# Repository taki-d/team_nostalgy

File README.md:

# team_nostalgy
for meister

# library
## web
https://github.com/nkapliev/nixie

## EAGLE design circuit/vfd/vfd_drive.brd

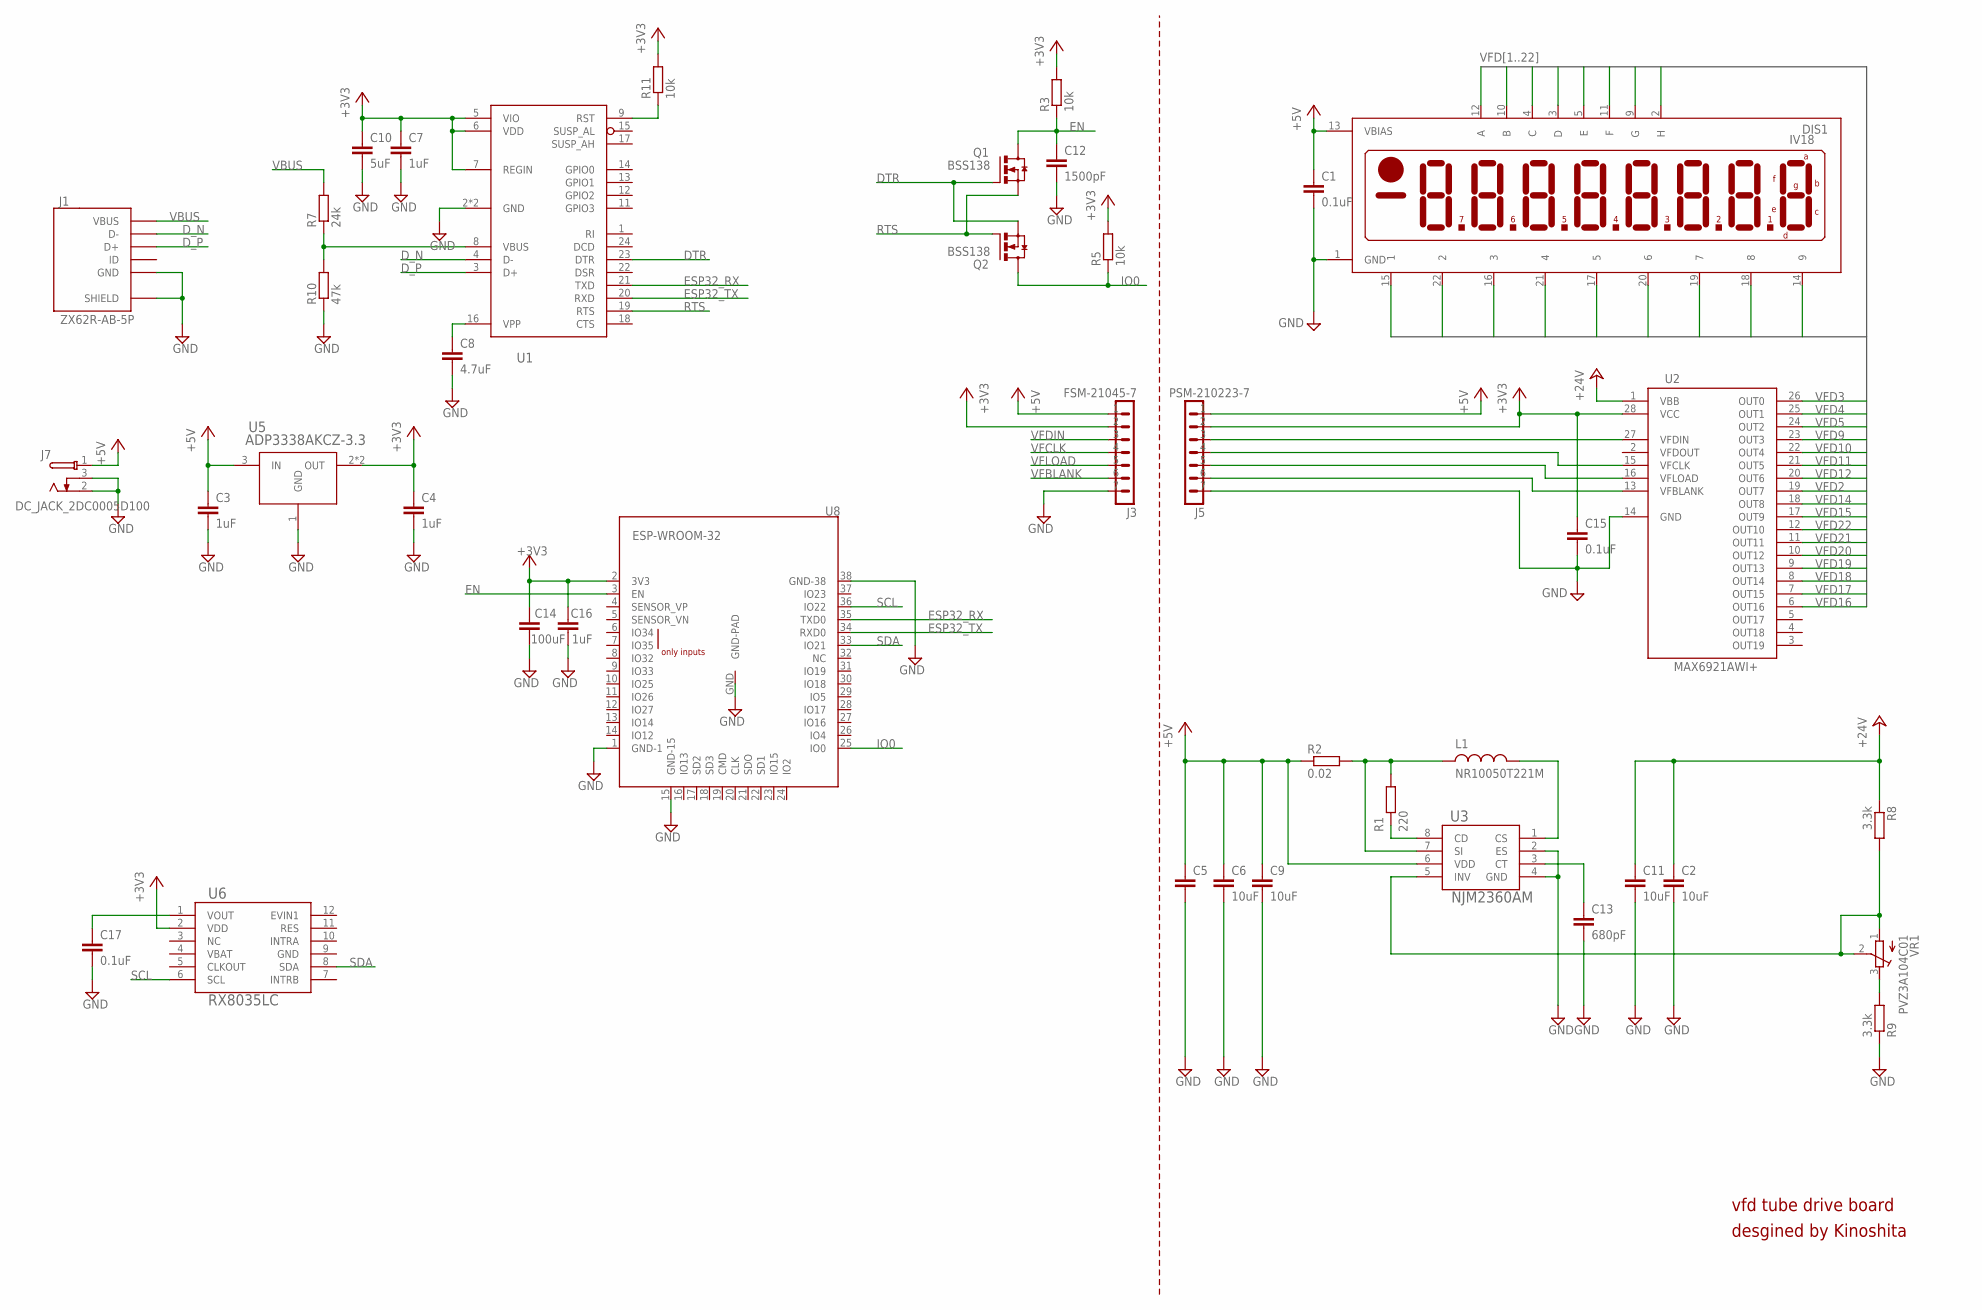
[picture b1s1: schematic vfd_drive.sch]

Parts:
C1, C15, C17: 0.1uF; C0603
C2, C11: 10uF; C3216
C3, C4, C7, C16: 1uF; C0603
C5: C-EUC3225; C3225
C6, C9: 10uF; C0603
C8: 4.7uF; C0603
C10: 5uF; C0603
C12: 1500pF; C0603
C13: 680pF; C0603
C14: 100uF; C1206
DIS1: IV18
J1: ZX62R-AB-5P; ZX62R-B-5PA
J3: FSM-21045-7
J5: PSM-210223-7
J7: DC_JACK_2DC0005D100
L1: NR10050T221M; NR10050T100M
Q1, Q2: BSS138; SOT23-N-MOSFET
R1: 220; R0603
R2: 0.02; R1206
R3, R5, R11: 10k; R0603
R7: 24k; R0603
R8, R9: 3.3k; R0603
R10: 47k; R0603
U1: CP2104; QFN24-SILABS
U2: MAX6921AWI+; SOIC-28-MI
U3: NJM2360AM; DMP8
U5: ADP3338AKCZ-3.3; SOT233
U6: RX8035LC; VSOJ12
U8: ESP-WROOM-32
VR1: PVZ3A104C01; PVZ3A

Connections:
+3V3: C4.1, C7.1, C10.1, C14.1, C15.1, C16.1, J3.2, J5.2, R3.2, R5.2, R11.2, U1.5 (VIO), U1.6 (VDD), U1.7 (REGIN), U2.28 (VCC), U5.2 (OUT), U5.4 (OUT), U6.2 (VDD), U8.2 (3V3)
+5V: C1.1, C3.1, C5.1, C6.1, C9.1, DIS1.13 (VBIAS), J3.1, J5.1, J7.1, R2.1, U3.6 (VDD), U5.3 (IN)
+24V: C2.1, C11.1, R8.1, U2.1 (VBB)
DTR: Q1.G, Q2.S, U1.23 (DTR)
D_N: J1.D-, U1.4 (D-)
D_P: J1.D+, U1.3 (D+)
EN: C12.1, Q1.D, R3.1, U8.3 (EN)
ESP32_RX: U1.21 (TXD), U8.35 (TXD0)
ESP32_TX: U1.20 (RXD), U8.34 (RXD0)
GND: C1.2, C2.2, C3.2, C4.2, C5.2, C6.2, C7.2, C8.2, C9.2, C10.2, C11.2, C12.2, C13.2, C14.2, C15.2, C16.2, C17.2, DIS1.1 (GND), J1.GND, J1.SHIELD@1 (SHIELD), J1.SHIELD@2 (SHIELD), J1.SHIELD@3 (SHIELD), J1.SHIELD@4 (SHIELD), J3.7, J5.7, J7.2, J7.3, R9.1, R10.1, U1.2 (GND), U1.25 (GND), U2.14 (GND), U3.2 (ES), U3.4 (GND), U5.1 (GND), U8.1 (GND-1), U8.15 (GND-15), U8.38 (GND-38), U8.GND (GND-PAD)
IO0: Q2.D, R5.1, U8.25 (IO0)
unnamed: R9.2, VR1.3 (A)
unnamed: C17.1, U6.1 (VOUT)
unnamed: J5.3, U2.27 (VFDIN)
unnamed: J5.4, U2.15 (VFCLK)
unnamed: J5.5, U2.16 (VFLOAD)
unnamed: L1.P$2 (2), U3.1 (CS)
unnamed: R11.1, U1.9 (RST)
unnamed: R7.1, R10.2, U1.8 (VBUS)
unnamed: C8.1, U1.16 (VPP)
unnamed: C13.1, U3.3 (CT)
unnamed: R8.2, U3.5 (INV), VR1.1 (E), VR1.2 (S)
unnamed: R1.1, U3.8 (CD)
unnamed: L1.P$1 (1), R1.2, R2.2, U3.7 (SI)
unnamed: J5.6, U2.13 (VFBLANK)
RTS: Q1.S, Q2.G, U1.19 (RTS)
SCL: U6.6 (SCL), U8.36 (IO22)
SDA: U6.8 (SDA), U8.33 (IO21)
VBUS: J1.VCC (VBUS), R7.2
VFBLANK: J3.6
VFCLK: J3.4
VFD2: DIS1.2 (H), U2.19 (OUT7)
VFD3: DIS1.3 (D), U2.26 (OUT0)
VFD4: DIS1.4 (C), U2.25 (OUT1)
VFD5: DIS1.5 (E), U2.24 (OUT2)
VFD9: DIS1.9 (G), U2.23 (OUT3)
VFD10: DIS1.10 (B), U2.22 (OUT4)
VFD11: DIS1.11 (F), U2.21 (OUT5)
VFD12: DIS1.12 (A), U2.20 (OUT6)
VFD14: DIS1.14 (9), U2.18 (OUT8)
VFD15: DIS1.15 (1), U2.17 (OUT9)
VFD16: DIS1.16 (3), U2.6 (OUT16)
VFD17: DIS1.17 (5), U2.7 (OUT15)
VFD18: DIS1.18 (8), U2.8 (OUT14)
VFD19: DIS1.19 (7), U2.9 (OUT13)
VFD20: DIS1.20 (6), U2.10 (OUT12)
VFD21: DIS1.21 (4), U2.11 (OUT11)
VFD22: DIS1.22 (2), U2.12 (OUT10)
VFDIN: J3.3
VFLOAD: J3.5

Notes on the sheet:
vfd tube drive board
desgined by Kinoshita

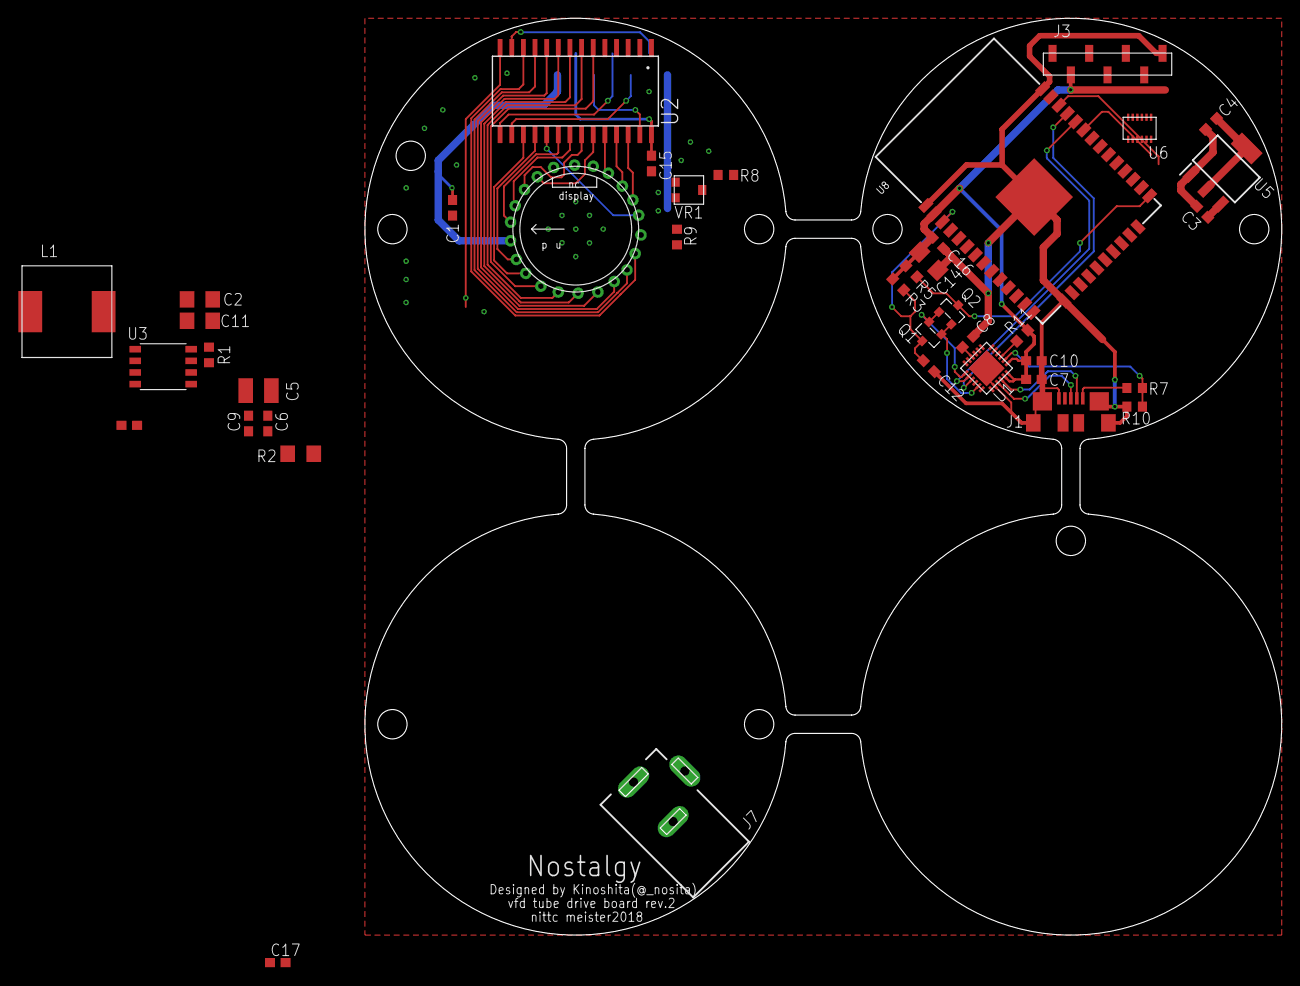
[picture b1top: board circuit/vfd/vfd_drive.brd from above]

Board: 2 copper layers, 100.0 x 100.0 mm, 41 parts (1 on the bottom side), 46 nets.

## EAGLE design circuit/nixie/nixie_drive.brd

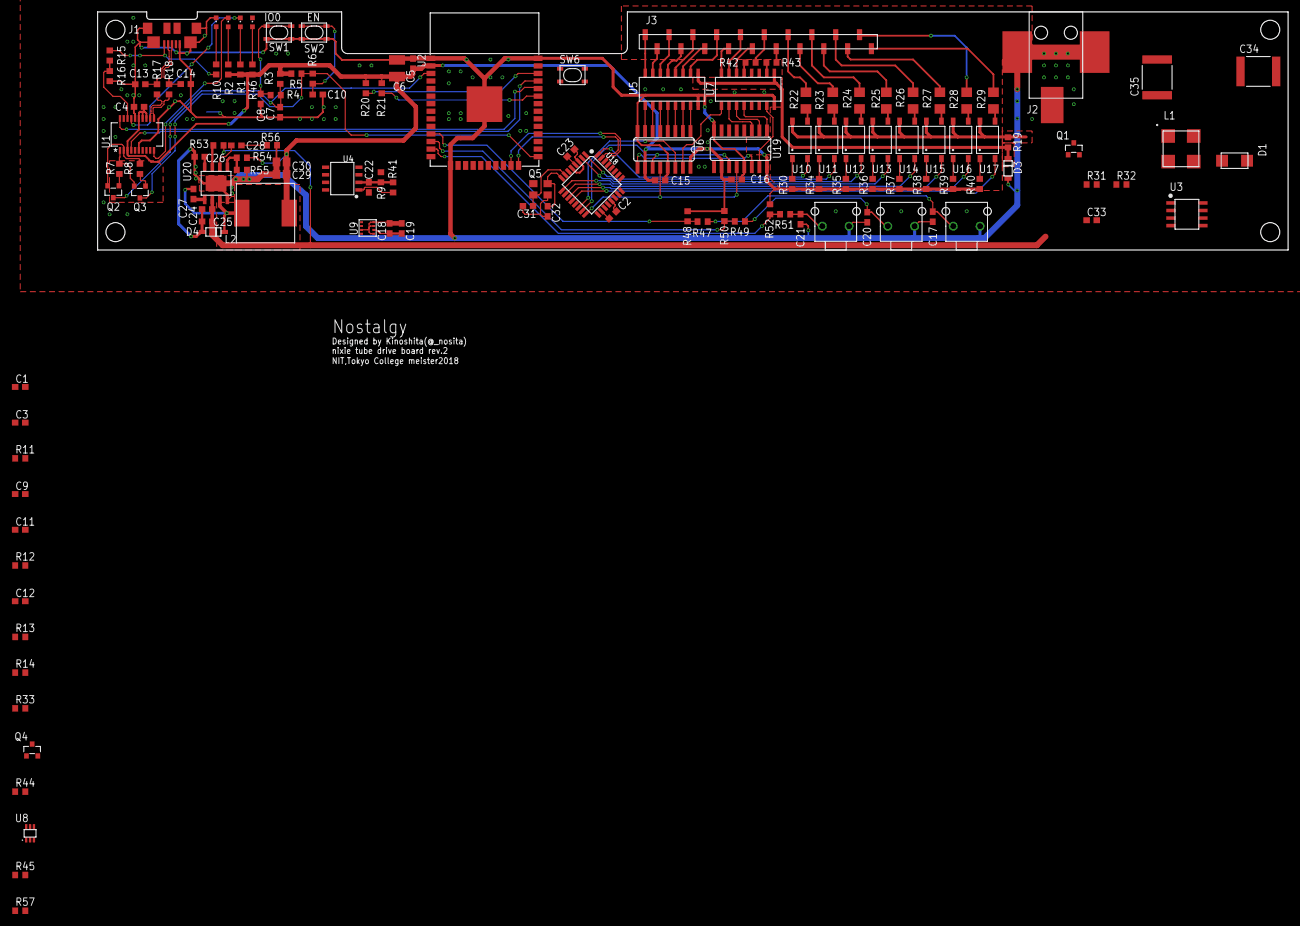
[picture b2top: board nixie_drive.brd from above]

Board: 2 copper layers, 200.0 x 40.0 mm, 136 parts (1 on the bottom side), 129 nets.

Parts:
BATT1: SMTU2032
C1, C3, C24, C25: 10uF; C0603
C2, C23: 0.1u; C0603
C4, C5, C11, C12, C15, C16, C18, C19, C22, C26: 0.1uF; C0603
C6: 100uF; C1210
C7, C8, C10, C17, C20, C21, C33: 1000pF; C0603
C9, C27: 10nF; C0603
C13, C14: 47pF; C0603
C28: 3.9nF; C0603
C29, C30: 22μF; C2012
C31, C32: 33p; C0603
C34, C35: 1u; C5750
D1: RFN2L4STE25; SOD-106
D3: MMSZ5267BT1G; SOD123
D4: B130LAW-7-F; DIODE-ZETEX-SOD123
J1: ZX62R-AB-5P; ZX62R-B-5PA
J2: 2DC-0415D200
J3: FSM-21045-20
L1: LPR6235
L2: NR10050T100M
LED1: RX; CHIPLED_0603
LED2: TX; CHIPLED_0603
LED3: VBUS; CHIPLED_0603
LED6: LED1; CHIPLED_0603
Q1, Q4: IRLML6344TRPBFTR; SOT23-N-MOSFET
Q2, Q3: MMSS8050-L; SOT23
Q5: FA-238V; FA238-V
R1, R2, R10, R12, R30, R34, R35, R36, R37, R38, R39, R40, R42, R43, R44, R46: 1k; R0603
R3, R5, R7, R8, R16, R31, R33, R48, R50, R52: 10k; R0603
R4, R6, R32, R47, R49, R51: 470; R0603
R9, R15, R20, R21, R41: 4.7k; R0603
R11: 0.1; R0603
R13: 20; R0603
R14: 174k; R0603
R17, R18: 27; R0603
R19: 220k; R0603
R22, R23, R24, R25, R26, R27, R28, R29: 10k; R3216
R45: 360k; R0603
R53: 100k; R0603
R54: 26.1k/1%; R0603
R55: 10k/1%; R0603
R56: 6.8k; R0603
R57: 2.4k; R0603
SW1, SW2, SW6: SKRPACE010
SW3, SW4, SW5: SKHHLPA010
U1: FT231XS; SSOP20_L
U2: ESP-WROOM-32
U3: LM3478; SOIC8-LT
U4: DS3231M; SO08
U5, U7: SN75468; R-PDSO-G16
U6, U19: 74HC595D; SO16
U8: MCP4017; SC-70-MICROCHIP
U9: BME280; LGA-8-2.5X2.5
U10, U11, U12, U13, U14, U15, U16, U17: TLP188; 11-4M1S
U18: ATMEGA328P-AU-TQFP32; TQFP32-0.8-7X7MM
U20: MP2307

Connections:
32KHZ: R41.1, U2.37, U4.1
+3V3: C2.1, C4.1, C5.1, C6.1, C15.1, C16.1, C18.1, C19.1, C22.1, C23.1, C29.1, C30.1, L2.P$2, R1.2, R2.2, R3.2, R5.2, R9.2, R20.2, R21.2, R30.1, R31.2, R34.1, R35.1, R36.1, R37.1, R38.1, R39.1, R40.1, R41.2, R46.2, R48.2, R50.2, R52.2, R54.2, U1.3, U1.13, U1.14, U1.15, U2.2, U4.2, U6.10, U6.16, U8.1, U9.2, U9.5, U9.6, U9.8, U18.4, U18.6, U18.18, U19.10, U19.16
+12V: C1.1, C3.1, C24.1, C25.1, J2.1, L1.1, R13.1, R33.2, R53.1, U20.2
+200V: C34.1, C35.1, D1.K, R19.2, R45.2, U10.6, U11.6, U12.6, U13.6, U14.6, U15.6, U16.6, U17.6
ANODE1: J3.13, R22.2
ANODE2: J3.14, R23.2
ANODE3: J3.15, R24.2
ANODE4: J3.16, R25.2
ANODE5: J3.17, R26.2
ANODE6: J3.18, R27.2
ANODE7: J3.19, R28.2
ANODE8: J3.20, R29.2
D2_N: R17.2, U1.12
D2_P: R18.2, U1.11
DTR: Q3.E, R7.2, U1.1
D_N: C13.1, J1.D-, R17.1
D_P: C14.1, J1.D+, R18.1
EN: C7.1, Q2.C, R3.1, R4.2, U2.3
ESP32_RX: U2.24, U18.31
ESP32_TX: U2.23, U18.30
FB: R57.2, U3.3, U8.5
GND: BATT1.N, C1.2, C2.2, C3.2, C4.2, C5.2, C6.2, C7.2, C8.1, C9.2, C10.1, C12.2, C13.2, C14.2, C15.2, C16.2, C17.1, C18.2, C19.2, C20.1, C21.1, C22.2, C23.2, C24.2, C25.2, C26.2, C29.2, C30.2, C31.2, C32.2, C33.1, C34.2, C35.2, D3.A, D4.A, J1.GND, J1.SHIELD@1, J1.SHIELD@2, J1.SHIELD@3, J1.SHIELD@4, J2.2, J2.3, LED3.C, Q4.S, Q5.2, Q5.4, R11.1, R12.1, R16.1, R55.1, R56.1, R57.1, SW1.P1, SW1.P2, SW2.P1, SW2.P2, SW3.1, SW4.1, SW5.1, SW6.P1, SW6.P2, U1.6, U1.16, U2.1, U2.15, U2.38, U2.GND, U3.4, U3.5, U4.5, U5.8, U6.8, U6.13, U7.8, U8.2, U9.1, U9.7, U18.3, U18.5, U18.21, U19.8, U19.13, U20.4, U20.PAD
IO0: Q3.C, R5.1, R6.2, U2.25
unnamed: D3.K, R19.1, U5.9, U7.9
unnamed: R15.1, R16.2, U1.18
unnamed: J3.1, U5.16
unnamed: LED1.C, U1.17
unnamed: LED2.C, U1.10
unnamed: C8.2, R4.1, SW1.S1, SW1.S2
unnamed: LED1.A, R1.1
unnamed: LED2.A, R2.1
unnamed: Q2.B, R7.1
unnamed: Q3.B, R8.1
unnamed: C32.1, Q5.3, U18.8
unnamed: C10.2, R6.1, SW2.S1, SW2.S2
unnamed: LED3.A, R10.1
unnamed: L1.2, L1.4, Q1.D
unnamed: C11.1, U3.2
unnamed: R14.2, U3.7
unnamed: U6.15, U7.1
unnamed: D1.A, L1.3
unnamed: Q1.G, U3.6
unnamed: C9.1, Q1.S, R11.2, U3.1
unnamed: C11.2, R12.2
unnamed: U5.7, U6.1
unnamed: C12.1, R13.2, U3.8
unnamed: Q4.D, R14.1, R33.1
unnamed: U5.6, U6.2
unnamed: U5.5, U6.3
unnamed: C31.1, Q5.1, U18.7
unnamed: R22.1, U10.4
unnamed: R23.1, U11.4
unnamed: R24.1, U12.4
unnamed: R25.1, U13.4
unnamed: R26.1, U14.4
unnamed: R27.1, U15.4
unnamed: R28.1, U16.4
unnamed: R29.1, U17.4
unnamed: R30.2, U10.1
unnamed: C33.2, R32.1, SW6.S1, SW6.S2
unnamed: U10.3, U18.32
unnamed: Q4.G, R44.2
unnamed: U5.4, U6.4
unnamed: U5.3, U6.5
unnamed: U5.2, U6.6
unnamed: U5.1, U6.7
unnamed: U6.9, U19.14
unnamed: U7.7, U19.15
unnamed: U7.4, U19.1
unnamed: U7.3, U19.2
unnamed: U7.2, U19.3
unnamed: R45.1, U8.6
unnamed: LED6.C, U2.8
unnamed: R34.2, U11.1
unnamed: R35.2, U12.1
unnamed: R36.2, U13.1
unnamed: R37.2, U14.1
unnamed: R38.2, U15.1
unnamed: R39.2, U16.1
unnamed: R40.2, U17.1
unnamed: U11.3, U18.1
unnamed: U12.3, U18.2
unnamed: U13.3, U18.9
unnamed: U14.3, U18.10
unnamed: U15.3, U18.11
unnamed: U16.3, U18.12
unnamed: U17.3, U18.13
unnamed: J3.2, U5.15
unnamed: J3.3, U5.14
unnamed: J3.4, U5.13
unnamed: J3.5, U5.12
unnamed: J3.6, U5.11
unnamed: J3.7, U5.10
unnamed: J3.8, U7.16
unnamed: J3.9, U7.15
unnamed: J3.10, U7.14
unnamed: J3.11, R42.2
unnamed: J3.12, R43.2
unnamed: R42.1, U7.13
unnamed: R43.1, U7.10
unnamed: C20.2, R49.1, SW4.2
unnamed: C17.2, R47.1, SW3.2
unnamed: R53.2, U20.7
unnamed: C26.1, U20.8
unnamed: C21.2, R51.1, SW5.2
unnamed: R54.1, R55.2, U20.5
unnamed: C27.2, U20.1
unnamed: C27.1, D4.K, L2.P$1, U20.3
unnamed: LED6.A, R46.1
unnamed: C28.1, U20.6
unnamed: C28.2, R56.2
RCK: U6.12, U18.16, U19.12
RST: R31.1, R32.2, U18.29
RTS: Q2.E, R8.2, U1.2
RXD: U1.4, U2.35
SCK: U6.11, U18.15, U19.11
SCL: R20.1, U2.36, U4.8, U9.4
SCL_AT: U8.3, U18.28
SDA: R21.1, U2.33, U4.7, U9.3
SDA_AT: U8.4, U18.27
SER: U6.14, U18.14
SQW: R9.1, U2.6, U4.3
SW3: R47.2, R48.1, U2.11
SW4: R49.2, R50.1, U2.12
SW5: R51.2, R52.1, U2.13
TXD: U1.20, U2.34
UC_EN: R44.1, U18.17
VBATT: BATT1.P, U4.6
VBUS: J1.VCC, R10.2, R15.2

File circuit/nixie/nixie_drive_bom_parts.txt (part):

Partlist exported from /home/taki/EAGLE/projects/nixie/nixie_drive.sch at 9/28/18 6:48 PM

Part  Value              Device             Package                         Description                                                             DIGIKEY_URL                                                                                             MARUTSU_URL                              PROD_ID  STORE   URL                                                                        VALUE  
BATT1 SMTU2032           SMTU2032           SMTU2032                                                                                                                                                                                                                                                                                                                                                    
C1    UWT1E221MNL1GS     UWT1E221MNL1GS     NICHICON-ALMINUM-CAPACITOR-8MM                                                                                                                                                                                                                                                                                                                              
C2    0.1uF              C-EUC0603          C0603                           CAPACITOR, European symbol                                                                                                                                                                                                                                                                                                  
C3    0.1uF              C-EUC0603          C0603                           CAPACITOR, European symbol                                                                                                                                                                                                                                                                                                  
C4    0.1uF              C-EUC0603          C0603                           CAPACITOR, European symbol                                                                                                                                                                                                                                                                                                  
C5    0.1uF              C-EUC0603          C0603                           CAPACITOR, European symbol                                                                                                                                                                                                                                                                                                  
C6    100uF              C-EUC1210          C1210                           CAPACITOR, European symbol                                                                                                                                                                                                                                                                                                  
C7    1000pF             C-EUC0603          C0603                           CAPACITOR, European symbol                                                                                                                                                                                                                                                                                                  
C8    1000pF             C-EUC0603          C0603                           CAPACITOR, European symbol                                                                                                                                                                                                                                                                                                  
C9    ULR2D330MML1GS     ULR2D330MML1GS     NICHICON-ALMINUM-CAPACITOR-10MM                                                                                                                                                                                                                                                                                                                             
C10   1000pF             C-EUC0603          C0603                           CAPACITOR, European symbol                                                                                                                                                                                                                                                                                                  
C11   0.1uF              C-EUC0603          C0603                           CAPACITOR, European symbol                                                                                                                                                                                                                                                                                                  
C12   330pF              C-EUC0603          C0603                           CAPACITOR, European symbol                                                                                                                                                                                                                                                                                                  
C13   47pF               C-EUC0603          C0603                           CAPACITOR, European symbol                                                                                                                                                                                                                                                                                                  
C14   47pF               C-EUC0603          C0603                           CAPACITOR, European symbol                                                                                                                                                                                                                                                                                                  
C15   0.1uF              C-EUC0603          C0603                           CAPACITOR, European symbol                                                                                                                                                                                                                                                                                                  
C16   0.1uF              C-EUC0603          C0603                           CAPACITOR, European symbol                                                                                                                                                                                                                                                                                                  
C17   1000pF             C-EUC0603          C0603                           CAPACITOR, European symbol                                                                                                                                                                                                                                                                                                  
C18   0.1uF              C-EUC0603          C0603                           CAPACITOR, European symbol                                                                                                                                                                                                                                                                                                  
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
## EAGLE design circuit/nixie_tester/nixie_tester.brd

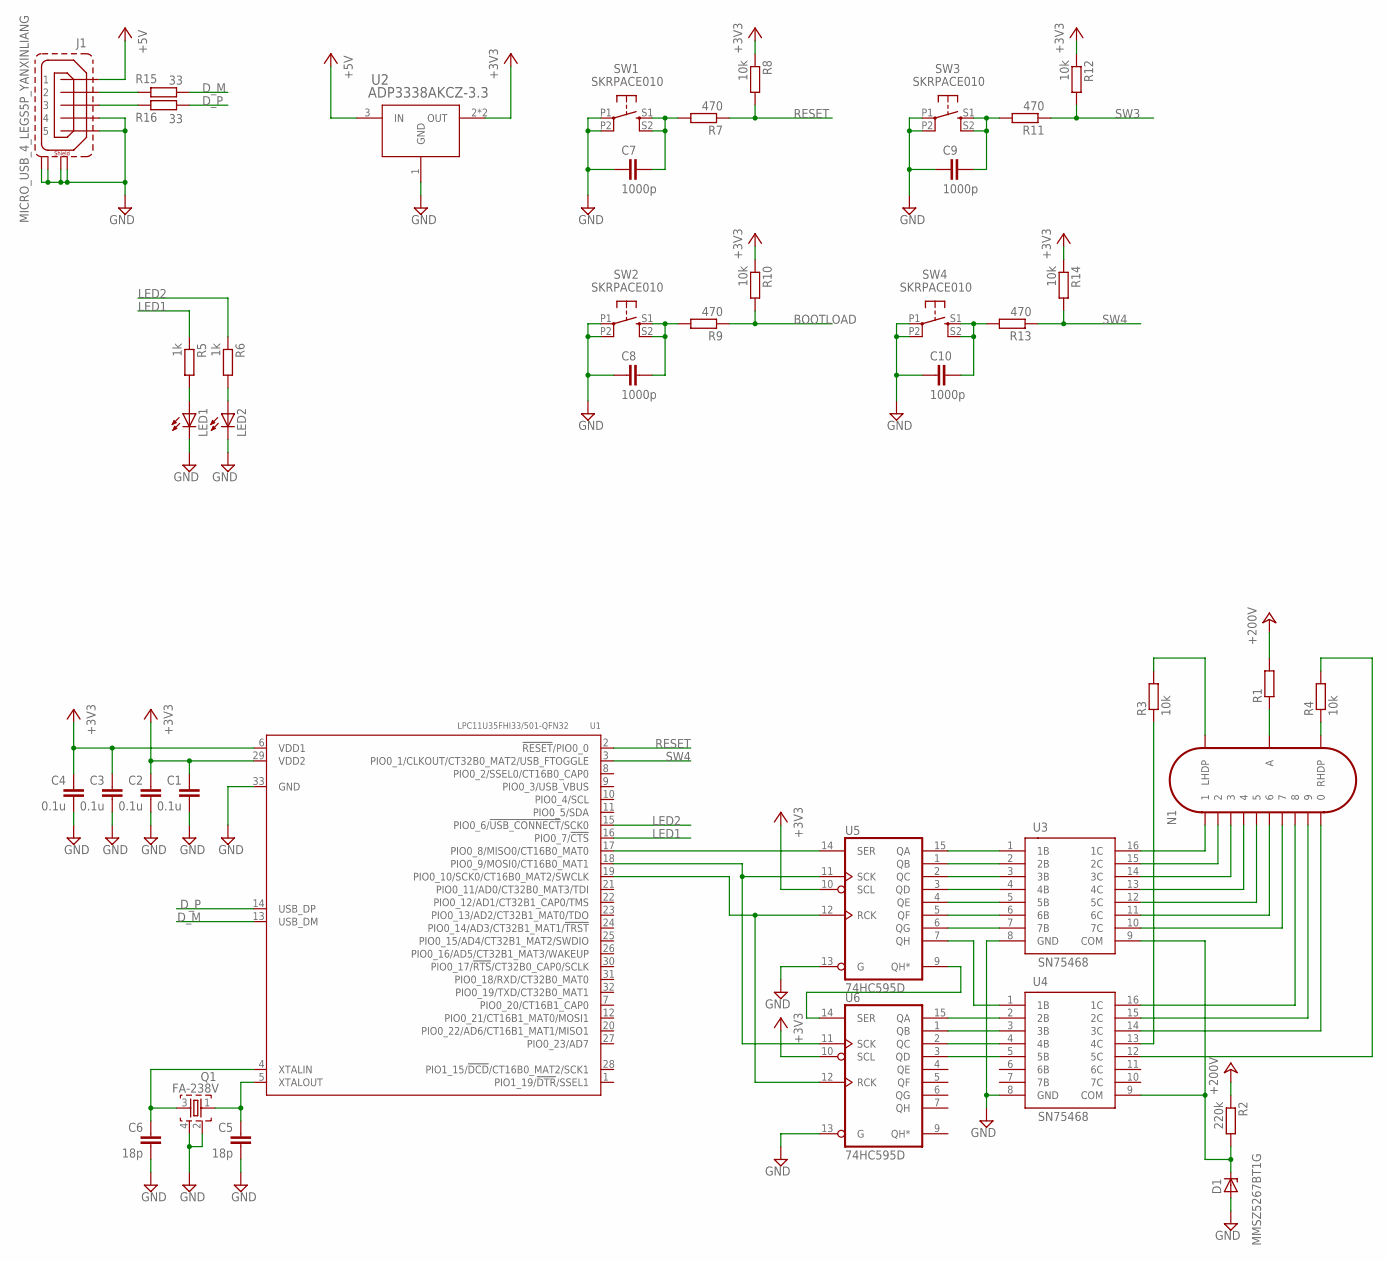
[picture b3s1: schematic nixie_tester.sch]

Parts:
C1, C2, C3, C4: 0.1u; C0603
C5, C6: 18p; C0603
C7, C8, C9, C10: 1000p; C0603
D1: MMSZ5267BT1G; SOD123
J1: MICRO_USB_4_LEGS5P_YANXINLIANG
LED1, LED2: LEDCHIPLED_0603; CHIPLED_0603
N1: IN-14
Q1: FA-238V; FA238-V
R1: R-EU_R1206; R1206
R2: 220k; R0603
R3, R4, R8, R10, R12, R14: 10k; R0603
R5, R6: 1k; R0603
R7, R9, R11, R13: 470; R0603
R15, R16: 33; R0603
SW1, SW2, SW3, SW4: SKRPACE010
U1: LPC11U35FHI33/501-QFN32; QFN32G-0.5-5X5MM
U2: ADP3338AKCZ-3.3; SOT233
U3, U4: SN75468; R-PDSO-G16
U5, U6: 74HC595D; SO16

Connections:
+3V3: C1.1, C2.1, C3.1, C4.1, R8.1, R10.1, R12.1, R14.1, U1.6 (VDD1), U1.29 (VDD2), U2.2 (OUT), U2.4 (OUT), U5.10 (SCL), U6.10 (SCL)
+5V: J1.1, U2.3 (IN)
+200V: R1.2, R2.1
BOOTLOAD: R9.1, R10.2
D_M: R15.1, U1.13 (USB_DM)
D_P: R16.1, U1.14 (USB_DP)
GND: C1.2, C2.2, C3.2, C4.2, C5.2, C6.2, C7.1, C8.1, C9.1, C10.1, D1.A, J1.4, J1.5, J1.S3, J1.S4, J1.S5, J1.S6, LED1.C, LED2.C, Q1.2, Q1.4, SW1.P1, SW1.P2 (P1), SW2.P1, SW2.P2 (P1), SW3.P1, SW3.P2 (P1), SW4.P1, SW4.P2 (P1), U1.33 (GND), U2.1 (GND), U3.8 (GND), U4.8 (GND), U5.8 (GND), U5.13 (G), U6.8 (GND), U6.13 (G)
LED1: R5.1, U1.16 (PIO0_7/!CTS!)
LED2: R6.1, U1.15 (PIO0_6/!USB_CONNECT!/SCK0)
unnamed: N1.1, U3.16 (1C)
unnamed: N1.2, U3.15 (2C)
unnamed: N1.3, U3.14 (3C)
unnamed: N1.4, U3.13 (4C)
unnamed: N1.5, U3.12 (5C)
unnamed: N1.6, U3.11 (6C)
unnamed: N1.7, U3.10 (7C)
unnamed: N1.8, U4.16 (1C)
unnamed: N1.9, U4.15 (2C)
unnamed: N1.0, U4.14 (3C)
unnamed: R3.1, U4.13 (4C)
unnamed: R4.2, U4.12 (5C)
unnamed: N1.A, R1.1
unnamed: D1.K (C), R2.2, U3.9 (COM), U4.9 (COM)
unnamed: N1.LHDP, R3.2
unnamed: N1.RHDP, R4.1
unnamed: LED1.A, R5.2
unnamed: C6.1, Q1.3, U1.4 (XTALIN)
unnamed: C5.1, Q1.1, U1.5 (XTALOUT)
unnamed: LED2.A, R6.2
unnamed: C7.2, R7.2, SW1.S1 (S), SW1.S2 (S1)
unnamed: C8.2, R9.2, SW2.S1 (S), SW2.S2 (S1)
unnamed: U3.1 (1B), U5.15 (QA)
unnamed: U3.2 (2B), U5.1 (QB)
unnamed: U3.3 (3B), U5.2 (QC)
unnamed: U3.4 (4B), U5.3 (QD)
unnamed: U3.5 (5B), U5.4 (QE)
unnamed: U3.6 (6B), U5.5 (QF)
unnamed: U3.7 (7B), U5.6 (QG)
unnamed: U4.1 (1B), U5.7 (QH)
unnamed: U5.9 (QH*), U6.14 (SER)
unnamed: U4.2 (2B), U6.15 (QA)
unnamed: U4.3 (3B), U6.1 (QB)
unnamed: U4.4 (4B), U6.2 (QC)
unnamed: U4.5 (5B), U6.3 (QD)
unnamed: U1.18 (PIO0_9/MOSI0/CT16B0_MAT1), U5.11 (SCK), U6.11 (SCK)
unnamed: U1.19 (PIO0_10/SCK0/CT16B0_MAT2/SWCLK), U5.12 (RCK), U6.12 (RCK)
unnamed: U1.17 (PIO0_8/MISO0/CT16B0_MAT0), U5.14 (SER)
unnamed: C9.2, R11.2, SW3.S1 (S), SW3.S2 (S1)
unnamed: C10.2, R13.2, SW4.S1 (S), SW4.S2 (S1)
unnamed: J1.2, R15.2
unnamed: J1.3, R16.2
RESET: R7.1, R8.2, U1.2 (!RESET!/PIO0_0)
SW3: R11.1, R12.2
SW4: R13.1, R14.2, U1.3 (PIO0_1/CLKOUT/CT32B0_MAT2/USB_FTOGGLE)
VCC: U5.16 (VCC), U6.16 (VCC)

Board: 2 copper layers, 42 parts (0 on the bottom side), 55 nets, no tracks yet.

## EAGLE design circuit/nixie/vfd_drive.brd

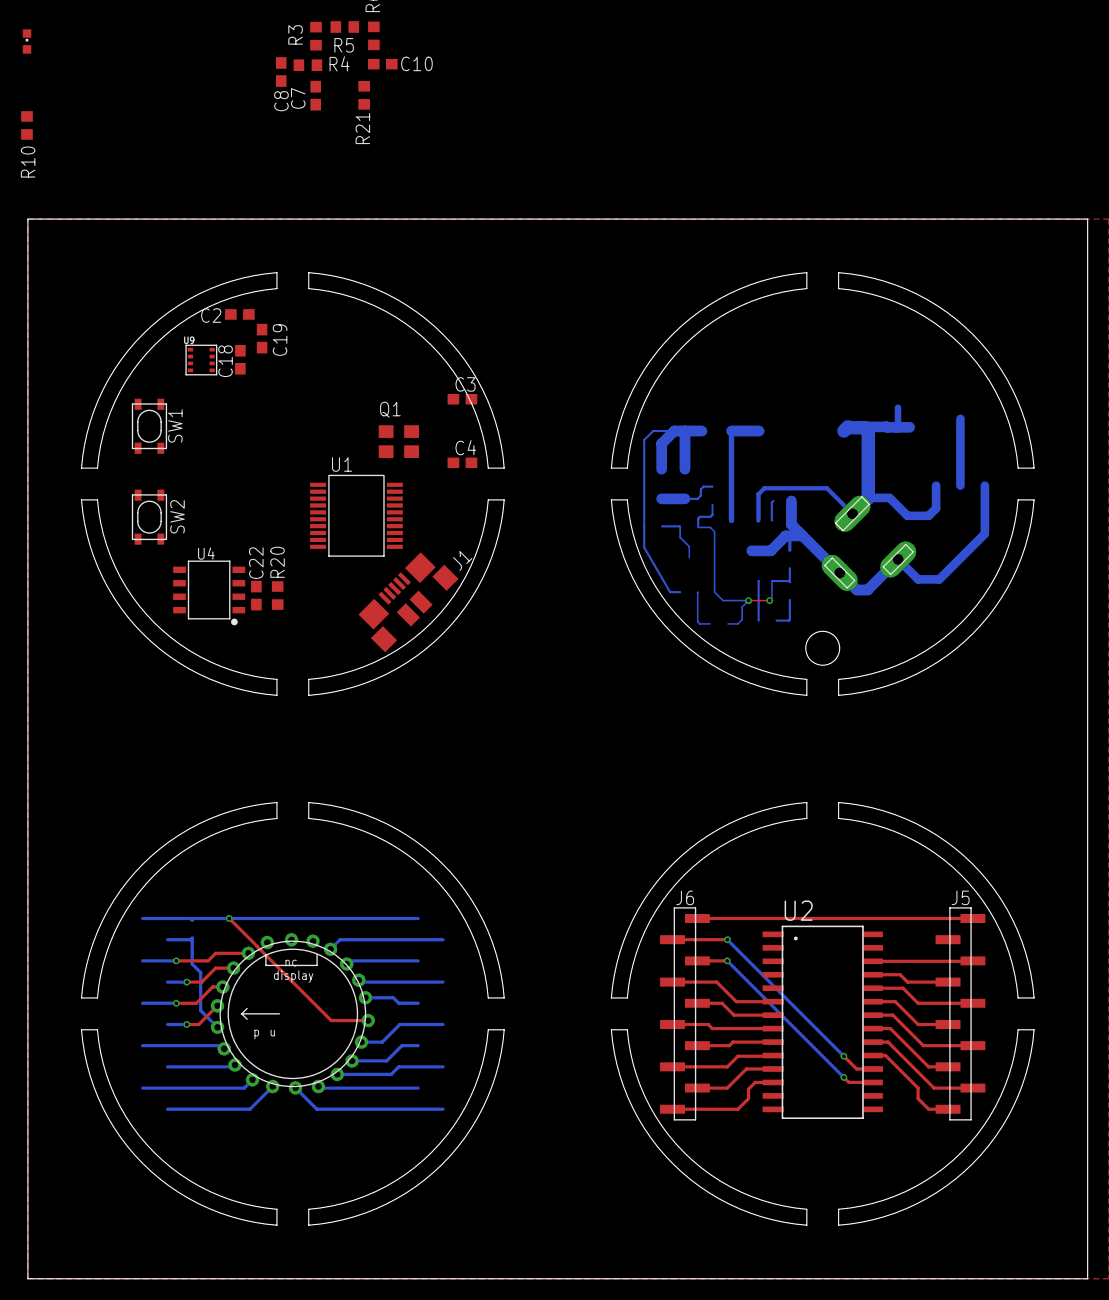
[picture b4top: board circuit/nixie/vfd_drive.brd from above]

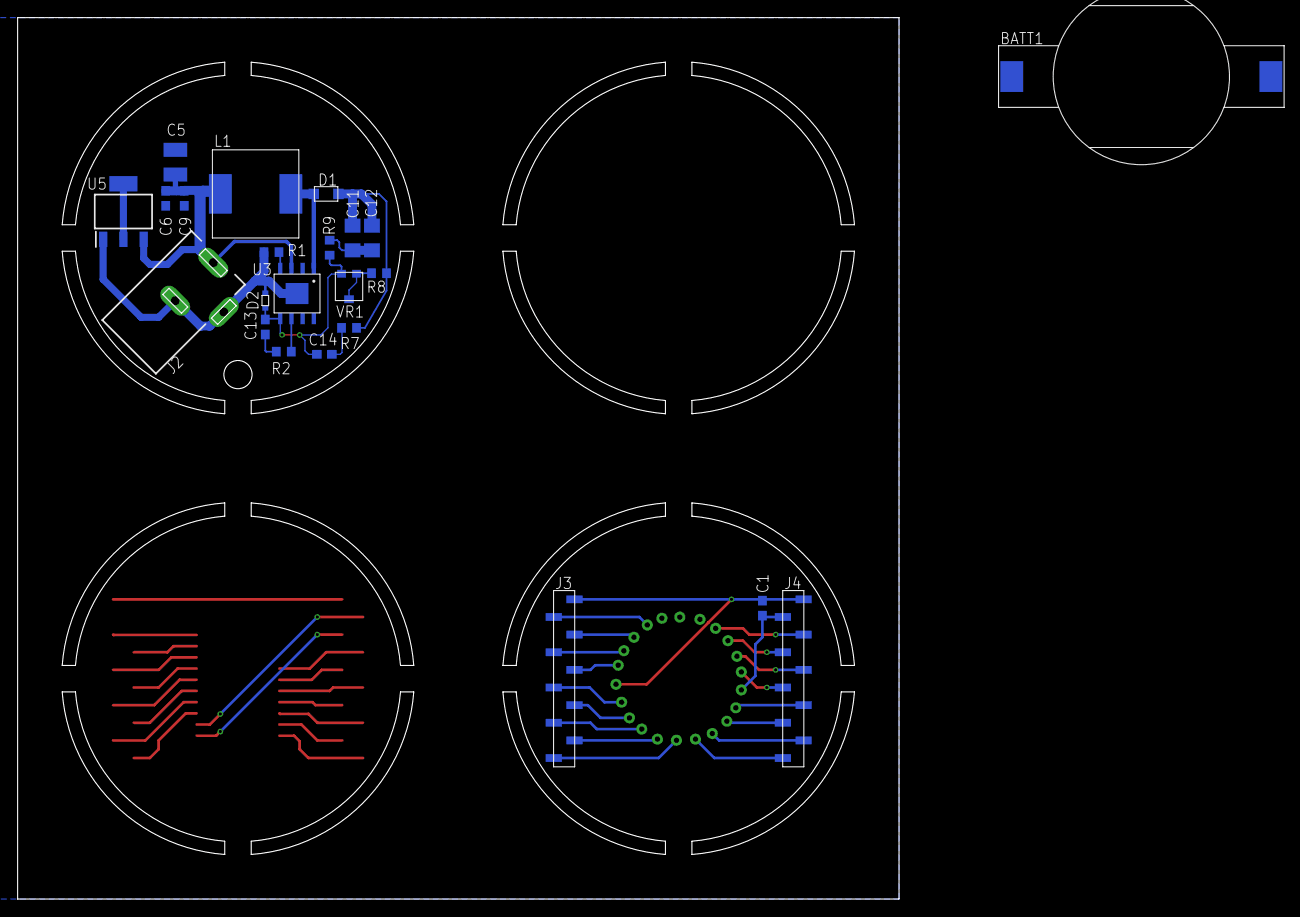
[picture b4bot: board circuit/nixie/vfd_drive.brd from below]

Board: 2 copper layers, 100.0 x 100.0 mm, 51 parts (23 on the bottom side), 60 nets.

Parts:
BATT1: SMTU2032
C1, C2, C18, C19, C22: 0.1uF; C0603
C3, C4: 15pF; C0603
C5: C3225
C6, C9, C13: 10uF; C0603
C7, C8, C10: 1000pF; C0603
C11, C12: 10uF; C3216
C14: 270pF; C0603
D1: SS2040FL; SOD-123FL
D2: BZX584C3V9; SOD-523
DIS1: IV18
J1: ZX62R-AB-5P; ZX62R-B-5PA
J2: DC_JACK_2DC0005D100
J3, J4: FSM-21045-10
J5, J6: PSM-210223-10
L1: NR10050T470M; NR10050T100M
LED3: VBUS; CHIPLED_0603
Q1: FA-238V; FA238-V
R1, R7: 27k; R0603
R2: 8.2k; R0603
R3, R5: 10k; R0603
R4, R6: 470; R0603
R8, R9: 3.3k; R0603
R10: 1k; R0603
R20, R21: 4.7k; R0603
SW1, SW2: SKRPACE010
U1: PIC18F14K50-I; SSOP20
U2: MAX6921AWI+; SOIC-28-MI
U3: NJW4131; HSOP8
U4: DS3231M; SO08
U5: ADP3338AKCZ-3.3; SOT233
U9: BME280; LGA-8-2.5X2.5
VR1: PVZ3A104C01; PVZ3A

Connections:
+3V3: C18.1, C19.1, C22.1, R3.2, R5.2, R20.2, R21.2, U4.2, U5.2, U5.4, U9.2, U9.5, U9.6, U9.8
+5V: C5.1, C6.1, C9.1, J2.1, L1.P$1, U1.1, U3.3, U5.3
+24V: C11.1, C12.1, D1.K, R7.1, R8.1
D_M: J1.D-, U1.18
D_P: J1.D+, U1.19
EN: C7.1, R3.1, R4.2
GND: BATT1.N, C1.2, C2.2, C3.2, C4.2, C5.2, C6.2, C7.2, C8.1, C9.2, C10.1, C11.2, C12.2, C18.2, C19.2, C22.2, D2.A, DIS1.1, J1.GND, J1.SHIELD@1, J1.SHIELD@2, J1.SHIELD@3, J1.SHIELD@4, J2.2, J2.3, J3.1, J4.1, J5.1, J6.1, LED3.C, Q1.2, Q1.4, R1.1, R9.1, SW1.P1, SW1.P2, SW2.P1, SW2.P2, U1.20, U3.7, U3.8, U3.PAD, U4.5, U5.1, U9.1, U9.7
IO0: R5.1, R6.2
unnamed: C8.2, R4.1, SW1.S1, SW1.S2
unnamed: C10.2, R6.1, SW2.S1, SW2.S2
unnamed: LED3.A, R10.1
unnamed: J5.3, U2.26
unnamed: J5.4, U2.25
unnamed: J5.5, U2.24
unnamed: J5.6, U2.23
unnamed: J5.7, U2.22
unnamed: J5.8, U2.21
unnamed: J5.9, U2.20
unnamed: J5.10, U2.19
unnamed: J6.2, U2.18
unnamed: J6.7, U2.9
unnamed: J6.8, U2.10
unnamed: J6.9, U2.11
unnamed: J6.10, U2.12
unnamed: J6.3, U2.17
unnamed: J6.6, U2.8
unnamed: J6.5, U2.7
unnamed: J6.4, U2.6
unnamed: C2.1, U1.17
unnamed: R1.2, U3.4
unnamed: D1.A, L1.P$2, U3.1
unnamed: R2.2, U3.6
unnamed: C3.1, Q1.1, U1.2
unnamed: C4.1, Q1.3, U1.3
unnamed: C13.1, R2.1
unnamed: C13.2, C14.1, D2.K, R9.2, U3.5, VR1.3
unnamed: C14.2, R7.2
unnamed: R8.2, VR1.1, VR1.2
SCL: R20.1, U1.11, U4.8, U9.4
SDA: R21.1, U1.13, U4.7, U9.3
VBATT: BATT1.P, U4.6
VBIAS: C1.1, DIS1.13, J4.2
VBUS: J1.VCC, R10.2
VFD2: DIS1.2, J3.5
VFD3: DIS1.3, J3.4
VFD4: DIS1.4, J3.3
VFD5: DIS1.5, J3.2
VFD9: DIS1.9, J4.3
VFD10: DIS1.10, J4.4
VFD11: DIS1.11, J4.5
VFD12: DIS1.12, J4.6
VFD14: DIS1.14, J4.7
VFD15: DIS1.15, J4.8
VFD16: DIS1.16, J4.9
VFD17: DIS1.17, J4.10
VFD18: DIS1.18, J3.10
VFD19: DIS1.19, J3.9
VFD20: DIS1.20, J3.8
VFD21: DIS1.21, J3.7
VFD22: DIS1.22, J3.6
